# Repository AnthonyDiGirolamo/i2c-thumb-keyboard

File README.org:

* i2c-thumb-keyboard

  Handheld tactile switch keyboard using the [[http://www.ti.com/product/TCA8418][TCA8418]].

  For more info see these [[https://hackaday.io/project/162281-teensy-thumb-keyboard][hackaday.io]] posts:
  - [[https://hackaday.io/project/162281-teensy-thumb-keyboard/log/164899-working-on-v2][Working on v2]]
  - [[https://hackaday.io/project/162281-teensy-thumb-keyboard/log/165015-raspberry-pi-i2c-connection][Raspberry Pi i2c Connection]]

** v1.0 Photo
   [[./images/v1.0-assembled.jpg]]

** BOM
   - 60x [[https://www.digikey.com/product-detail/en/panasonic-electronic-components/EVQ-Q2B03W/P12932SCT-ND/762922][EVQ-Q2B03W Tactile Switch]] (SW1-SW60)
   - 10x [[https://lcsc.com/product-detail/Switching-Diode_1N4148WS_C110221.html][1N4148WS Diode]] (D1-D10)
   - 1x [[https://lcsc.com/product-detail/Interface-ICs_TI_TCA8418RTWR_TCA8418RTWR_C138713.html][TCA8418]]
   - 2x [[https://lcsc.com/product-detail/Chip-Resistor-Surface-Mount_Uniroyal-Elec-0603WAF1002T5E_C25804.html][0603 10k Resistor]] (R1, R4)
   - 2x [[https://lcsc.com/product-detail/Chip-Resistor-Surface-Mount_Uniroyal-Elec-0603WAF4701T5E_C23162.html][0603 4.7k Resistor]] (R2, R3)
   - 2x [[https://lcsc.com/product-detail/Multilayer-Ceramic-Capacitors-MLCC-SMD-SMT_SAMSUNG_CL10B104KA8NNNC_100nF-104-10-25V_C1590.html][0603 0.1uF Capacitor]] (C1, C2)
   - 1x [[https://lcsc.com/product-detail/Multilayer-Ceramic-Capacitors-MLCC-SMD-SMT_SAMSUNG_CL10A106MQ8NNNC_10uF-106-20-6-3V_C1691.html][0603 10uF Capacitor]] (C3)
   - Optional:
     - 1x [[https://www.digikey.com/product-detail/en/jst-sales-america-inc/S4B-PH-SM4-TB(LF)(SN)/455-1751-1-ND/926848][JST PH Connector Socket S4B-PH-SM4-TB(LF)(SN)]]
     - 1x [[https://www.digikey.com/product-detail/en/jst-sales-america-inc/A04KR04KR26E152B/455-3151-ND/6194806][JST KR Jumper Cable]]

** Prior Work

   [[https://github.com/AnthonyDiGirolamo/teensy-thumb-keyboard][teensy-thumb-keyboard]]

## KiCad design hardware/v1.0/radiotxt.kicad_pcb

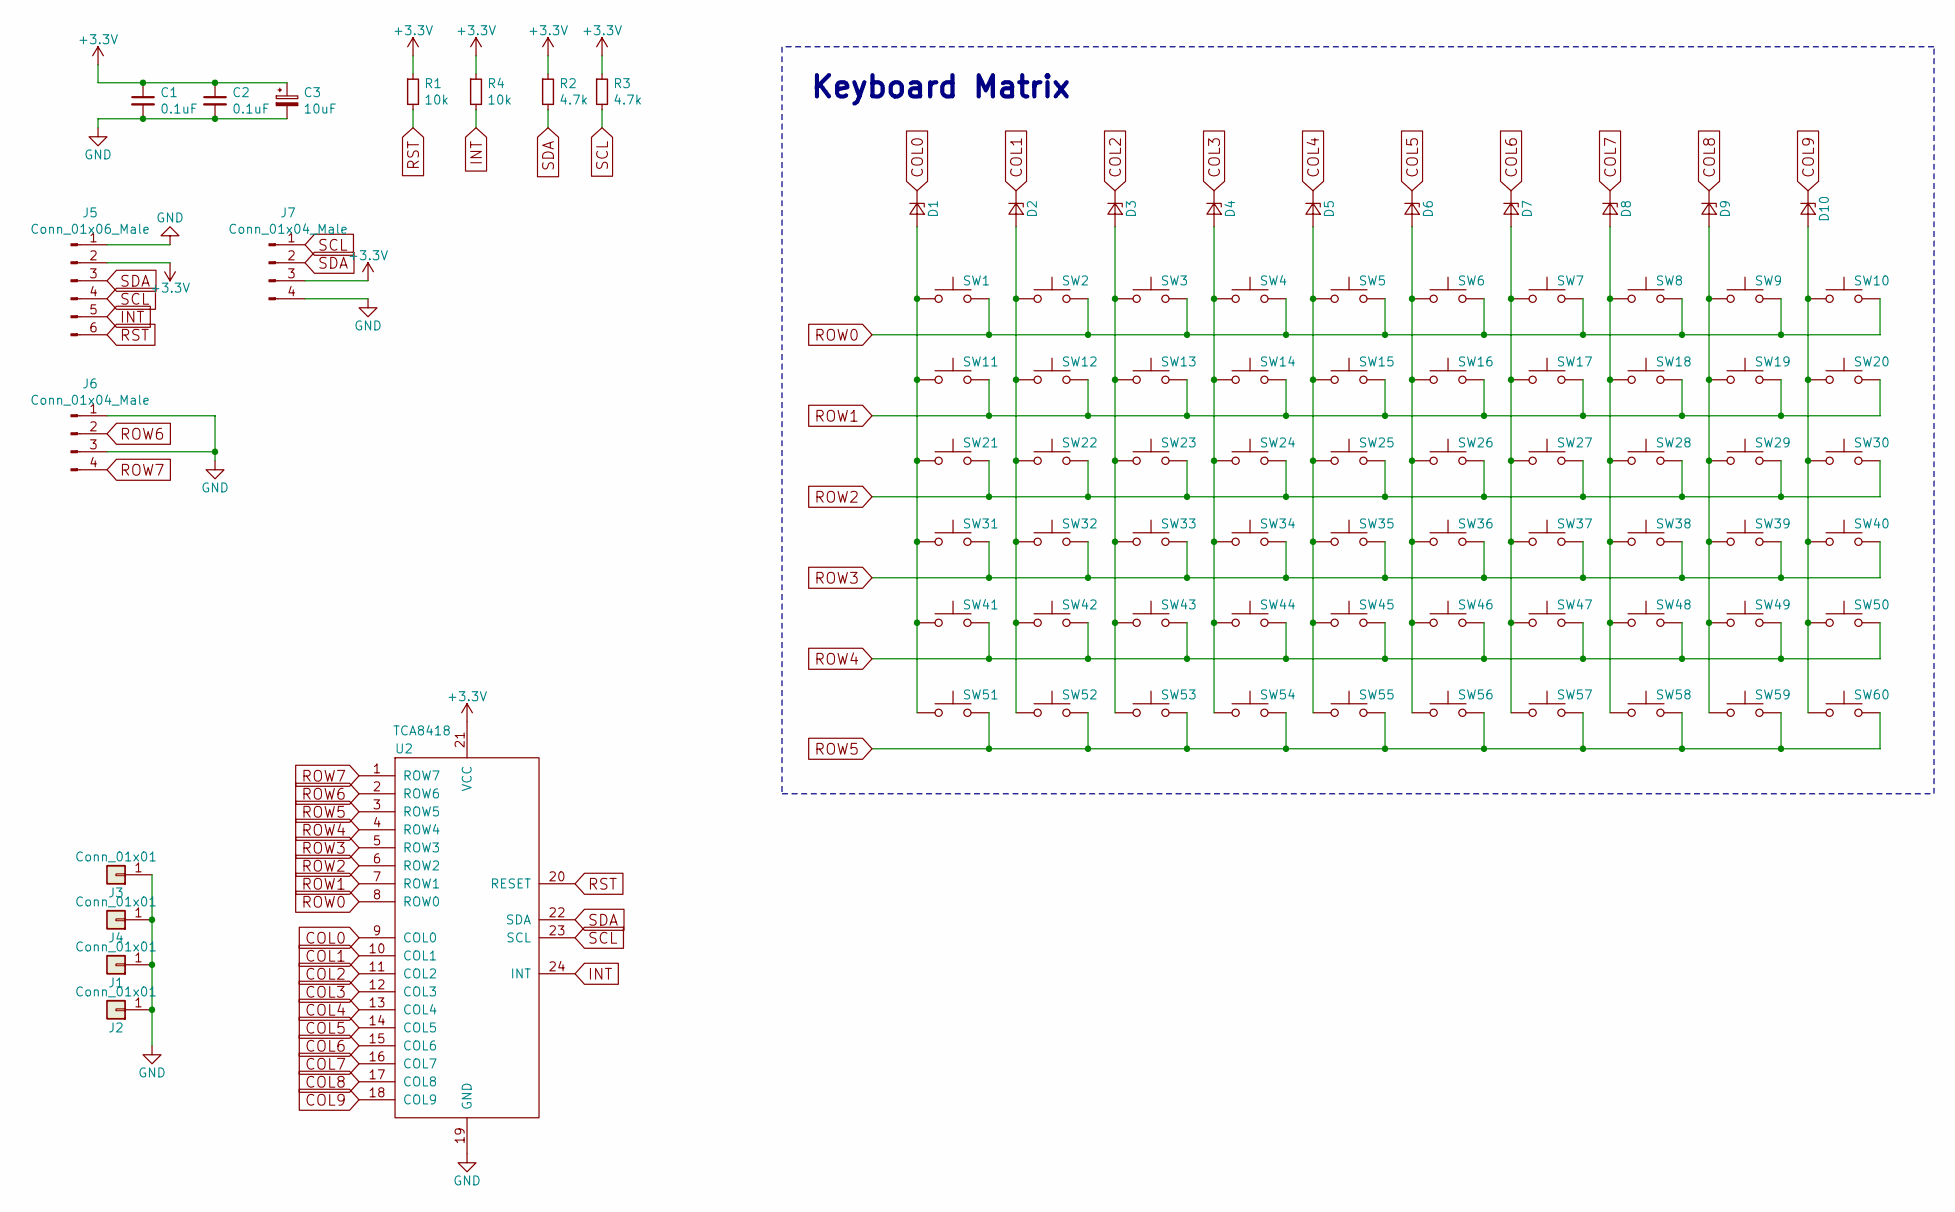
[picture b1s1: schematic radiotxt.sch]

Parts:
C1, C2: 0.1uF; C_0603_1608Metric_Pad1.05x0.95mm_HandSolder
C3: 10uF; C_0603_1608Metric_Pad1.05x0.95mm_HandSolder
D1, D2, D3, D4, D5, D6, D7, D8, D9, D10: D_Zener_Small; D_SOD-323_HandSoldering
J1, J2, J3, J4: Conn_01x01; 2.5MountingHole
J5: Conn_01x06_Male; PinHeader_1x06_P2.54mm_Vertical
J6: Conn_01x04_Male; PinSocket_1x04_P2.54mm_Vertical
J7: Conn_01x04_Male; JST_PH_S4B-PH-SM4-TB_1x04-1MP_P2.00mm_Horizontal
R1, R4: 10k; R_0603_1608Metric_Pad1.05x0.95mm_HandSolder
R2, R3: 4.7k; R_0603_1608Metric_Pad1.05x0.95mm_HandSolder
SW1, SW2, SW3, SW4, SW5, SW6, SW7, SW8, SW9, SW10, SW11, SW12, SW13, SW14, SW15, SW16, SW17, SW18, SW19, SW20, SW21, SW22, SW23, SW24, SW25, SW26, SW27, SW28, SW29, SW30, SW31, SW32, SW33, SW34, SW35, SW36, SW37, SW38, SW39, SW40, SW41, SW42, SW43, SW44, SW45, SW46, SW47, SW48, SW49, SW50, SW51, SW52, SW53, SW54, SW55, SW56, SW57, SW58, SW59, SW60: SW_Push; SW_SPST_EVQQ2
U2: TCA8418; WQFN-24-1EP_4x4mm_P0.5mm_EP2.7x2.7mm

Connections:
+3V3: C1.1, C2.1, C3.1, J5.2, J7.3, R1.1, R2.1, R3.1, R4.1, U2.21 (VCC)
COL0: D1.1 (K), U2.9 (COL0)
COL1: D2.1 (K), U2.10 (COL1)
COL2: D3.1 (K), U2.11 (COL2)
COL3: D4.1 (K), U2.12 (COL3)
COL4: D5.1 (K), U2.13 (COL4)
COL5: D6.1 (K), U2.14 (COL5)
COL6: D7.1 (K), U2.15 (COL6)
COL7: D8.1 (K), U2.16 (COL7)
COL8: D9.1 (K), U2.17 (COL8)
COL9: D10.1 (K), U2.18 (COL9)
GND: C1.2, C2.2, C3.2, J1.1, J2.1, J3.1, J4.1, J5.1, J6.1, J6.3, J7.4, U2.19 (GND)
INT: J5.5, R4.2, U2.24 (INT)
unnamed: D1.2 (A), SW1.1, SW11.1, SW21.1, SW31.1, SW41.1, SW51.1
unnamed: D2.2 (A), SW2.1, SW12.1, SW22.1, SW32.1, SW42.1, SW52.1
unnamed: D3.2 (A), SW3.1, SW13.1, SW23.1, SW33.1, SW43.1, SW53.1
unnamed: D4.2 (A), SW4.1, SW14.1, SW24.1, SW34.1, SW44.1, SW54.1
unnamed: D5.2 (A), SW5.1, SW15.1, SW25.1, SW35.1, SW45.1, SW55.1
unnamed: D6.2 (A), SW6.1, SW16.1, SW26.1, SW36.1, SW46.1, SW56.1
unnamed: D7.2 (A), SW7.1, SW17.1, SW27.1, SW37.1, SW47.1, SW57.1
unnamed: D8.2 (A), SW8.1, SW18.1, SW28.1, SW38.1, SW48.1, SW58.1
unnamed: D9.2 (A), SW9.1, SW19.1, SW29.1, SW39.1, SW49.1, SW59.1
unnamed: D10.2 (A), SW10.1, SW20.1, SW30.1, SW40.1, SW50.1, SW60.1
ROW0: SW1.2, SW2.2, SW3.2, SW4.2, SW5.2, SW6.2, SW7.2, SW8.2, SW9.2, SW10.2, U2.8 (ROW0)
ROW1: SW11.2, SW12.2, SW13.2, SW14.2, SW15.2, SW16.2, SW17.2, SW18.2, SW19.2, SW20.2, U2.7 (ROW1)
ROW2: SW21.2, SW22.2, SW23.2, SW24.2, SW25.2, SW26.2, SW27.2, SW28.2, SW29.2, SW30.2, U2.6 (ROW2)
ROW3: SW31.2, SW32.2, SW33.2, SW34.2, SW35.2, SW36.2, SW37.2, SW38.2, SW39.2, SW40.2, U2.5 (ROW3)
ROW4: SW41.2, SW42.2, SW43.2, SW44.2, SW45.2, SW46.2, SW47.2, SW48.2, SW49.2, SW50.2, U2.4 (ROW4)
ROW5: SW51.2, SW52.2, SW53.2, SW54.2, SW55.2, SW56.2, SW57.2, SW58.2, SW59.2, SW60.2, U2.3 (ROW5)
ROW6: J6.2, U2.2 (ROW6)
ROW7: J6.4, U2.1 (ROW7)
RST: J5.6, R1.2, U2.20 (RESET)
SCL: J5.4, J7.1, R3.2, U2.23 (SCL)
SDA: J5.3, J7.2, R2.2, U2.22 (SDA)

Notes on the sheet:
Keyboard Matrix

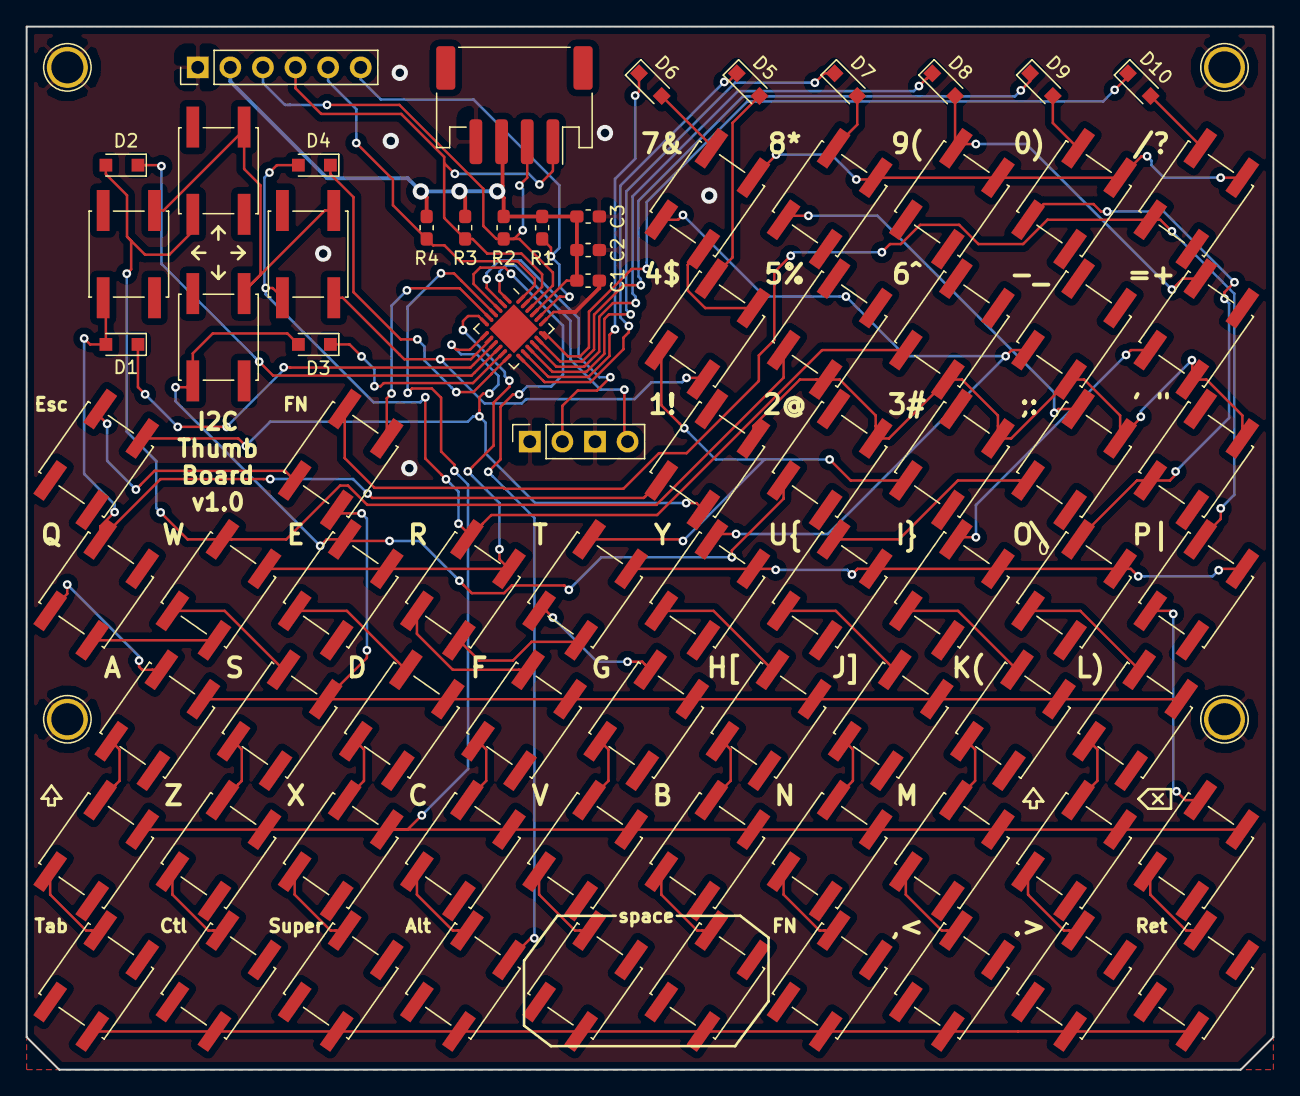
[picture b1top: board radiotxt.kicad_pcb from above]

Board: 2 copper layers, 97.2 x 81.3 mm, 85 parts (0 on the bottom side), 34 nets.

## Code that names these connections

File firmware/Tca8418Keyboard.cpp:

#include "Tca8418Keyboard.h"

Tca8418Keyboard::Tca8418Keyboard(uint8_t numrows, uint8_t numcols) {
  tca8418_address = TCA8418_I2C_ADDRESS;
  num_rows = numrows;
  num_cols = numcols;

  delta_micros = 0;
  last_update_micros = 0;
  this_update_micros = 0;

  pressed_list = new PressedKey[KEY_EVENT_LIST_SIZE];
  released_list = new ReleasedKey[KEY_EVENT_LIST_SIZE];
  matrix_state = new uint16_t[num_rows];
  matrix_state_prev = new uint16_t[num_rows];

}

Tca8418Keyboard::~Tca8418Keyboard(void) {
  delete [] matrix_state_prev;
  delete [] matrix_state;
  delete [] pressed_list;
  delete [] released_list;
}

void Tca8418Keyboard::begin(void) {
  Wire.begin();

  /*
    | ADDRESS | REGISTER NAME | REGISTER DESCRIPTION | BIT7 | BIT6 | BIT5 | BIT4 | BIT3 | BIT2 | BIT1 | BIT0 |
    |---------+---------------+----------------------+------+------+------+------+------+------+------+------|
    |    0x1D | KP_GPIO1      | Keypad/GPIO Select 1 | ROW7 | ROW6 | ROW5 | ROW4 | ROW3 | ROW2 | ROW1 | ROW0 |
    |    0x1E | KP_GPIO2      | Keypad/GPIO Select 2 | COL7 | COL6 | COL5 | COL4 | COL3 | COL2 | COL1 | COL0 |
    |    0x1F | KP_GPIO3      | Keypad/GPIO Select 3 | N/A  | N/A  | N/A  | N/A  | N/A  | N/A  | COL9 | COL8 |
  */

  // everything enabled in key scan mode
  uint8_t enabled_rows = 0x3F;
  uint16_t enabled_cols = 0x3FF;

  write(REGISTER_KP_GPIO1, enabled_rows);
  write(REGISTER_KP_GPIO2, (uint8_t)(0xFF & enabled_cols));
  write(REGISTER_KP_GPIO3, (uint8_t)(0x03 & (enabled_cols >> 8)));

  /*
    BIT: NAME

    7: AI
    Auto-increment for read and write operations; See below table for more information
    0 = disabled
    1 = enabled

    6: GPI_E_CFG
    GPI event mode configuration
    0 = GPI events are tracked when keypad is locked
    1 = GPI events are not tracked when keypad is locked

    5: OVR_FLOW_M
    Overflow mode
    0 = disabled; Overflow data is lost
    1 = enabled; Overflow data shifts with last event pushing first event out

    4: INT_CFG
    Interrupt configuration
    0 = processor interrupt remains asserted (or low) if host tries to clear interrupt while there is
    still a pending key press, key release or GPI interrupt
    1 = processor interrupt is deasserted for 50 μs and reassert with pending interrupts

    3: OVR_FLOW_IEN
    Overflow interrupt enable
    0 = disabled; INT is not asserted if the FIFO overflows
    1 = enabled; INT becomes asserted if the FIFO overflows

    2: K_LCK_IEN
    Keypad lock interrupt enable
    0 = disabled; INT is not asserted after a correct unlock key sequence
    1 = enabled; INT becomes asserted after a correct unlock key sequence

    1: GPI_IEN
    GPI interrupt enable to host processor
    0 = disabled; INT is not asserted for a change on a GPI
    1 = enabled; INT becomes asserted for a change on a GPI

    0: KE_IEN
    Key events interrupt enable to host processor
    0 = disabled; INT is not asserted when a key event occurs
    1 = enabled; INT becomes asserted when a key event occurs
   */

  // 10111001 xB9 -- fifo overflow enabled
  // 10011001 x99 -- fifo overflow disabled
  write(REGISTER_CFG, 0x99);

  clear_released_list();
  clear_pressed_list();

  delayMicroseconds(100);
}

void Tca8418Keyboard::write(uint8_t register_address, uint8_t data) {
  Wire.beginTransmission(tca8418_address);
  Wire.write((uint8_t) register_address);
  Wire.write((uint8_t) data);
  Wire.endTransmission();
}

bool Tca8418Keyboard::read(uint8_t register_address, uint8_t *data) {
  Wire.beginTransmission(tca8418_address);
  Wire.write(register_address);
  Wire.endTransmission();

  uint8_t timeout=0;
  Wire.requestFrom(tca8418_address, (uint8_t) 0x01);

  while(Wire.available() < 1) {
    timeout++;
    if(timeout > 100) {
      return false;
    }
    delayMicroseconds(1);
  }
  *data = Wire.read();
  return true;
}

bool Tca8418Keyboard::update() {
  last_update_micros = this_update_micros;
  uint8_t key_code, key_down, key_event, key_row, key_col;

  key_event = get_key_event();
  // TODO: read gpio R7/R6 status? 0x14 bits 7&6
  // read(0x14, &new_keycode)

  this_update_micros = micros();
  delta_micros = this_update_micros - last_update_micros;

  // if there is a new event
  if (key_event > 0) {
    key_code = key_event & 0x7F;
    key_down = (key_event & 0x80) >> 7;
    key_row = key_code / num_cols;
    key_col = key_code % num_cols;

    Serial.println(key_code);
    Serial.println(key_down);

    // always clear the released list
    clear_released_list();

    if (key_down) {
      add_pressed_key(key_row, key_col);
      // TODO reject ghosts (assume multiple key presses with the same hold time are ghosts.)

    }
    else {
      add_released_key(key_row, key_col);
      remove_pressed_key(key_row, key_col);
    }

    return true;
  }

  // increment hold times for pressed keys
  for (int i=0; i<pressed_key_count; i++) {
    pressed_list[i].hold_time += delta_micros;
  }

  return false;
}


void Tca8418Keyboard::add_pressed_key(uint8_t row, uint8_t col) {
  if (pressed_key_count >= KEY_EVENT_LIST_SIZE)
    return;

  pressed_list[pressed_key_count].row = row;
  pressed_list[pressed_key_count].col = col;
  pressed_list[pressed_key_count].hold_time = 0;
  pressed_key_count++;
}

void Tca8418Keyboard::add_released_key(uint8_t row, uint8_t col) {
  if (released_key_count >= KEY_EVENT_LIST_SIZE)
    return;

  released_key_count++;
  released_list[0].row = row;
  released_list[0].col = col;
}


void Tca8418Keyboard::remove_pressed_key(uint8_t row, uint8_t col) {
  if (pressed_key_count == 0)
    return;

  // delete the pressed key
  for (int i=0; i<pressed_key_count; i++) {
    if (pressed_list[i].row == row &&
        pressed_list[i].col == col) {
      // shift remaining keys left one index
      for (int j=i; i<pressed_key_count; j++) {
        if (j == KEY_EVENT_LIST_SIZE - 1)
          break;
        pressed_list[j].row = pressed_list[j+1].row;
        pressed_list[j].col = pressed_list[j+1].col;
        pressed_list[j].hold_time = pressed_list[j+1].hold_time;
      }
      break;
    }
  }
  pressed_key_count--;
}

void Tca8418Keyboard::clear_pressed_list() {
  for (int i=0; i<KEY_EVENT_LIST_SIZE; i++) {
    pressed_list[i].row = 255;
    pressed_list[i].col = 255;
  }
  pressed_key_count = 0;
}

void Tca8418Keyboard::clear_released_list() {
  for (int i=0; i<KEY_EVENT_LIST_SIZE; i++) {
    released_list[i].row = 255;
    released_list[i].col = 255;
  }
  released_key_count = 0;
}

uint8_t Tca8418Keyboard::get_key_event() {
  uint8_t new_keycode = 0;

  read(REGISTER_KEY_EVENT_A, &new_keycode);
  return(new_keycode);
}

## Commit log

2020-02-24 Add README and LICENSE
2020-02-24 Add v1.0 kicad files
2020-02-24 Update readme, add photos
2020-02-24 Add hackaday.io and prior work links
2020-05-27 add example arduino firmware code
2023-09-17 License as MIT
